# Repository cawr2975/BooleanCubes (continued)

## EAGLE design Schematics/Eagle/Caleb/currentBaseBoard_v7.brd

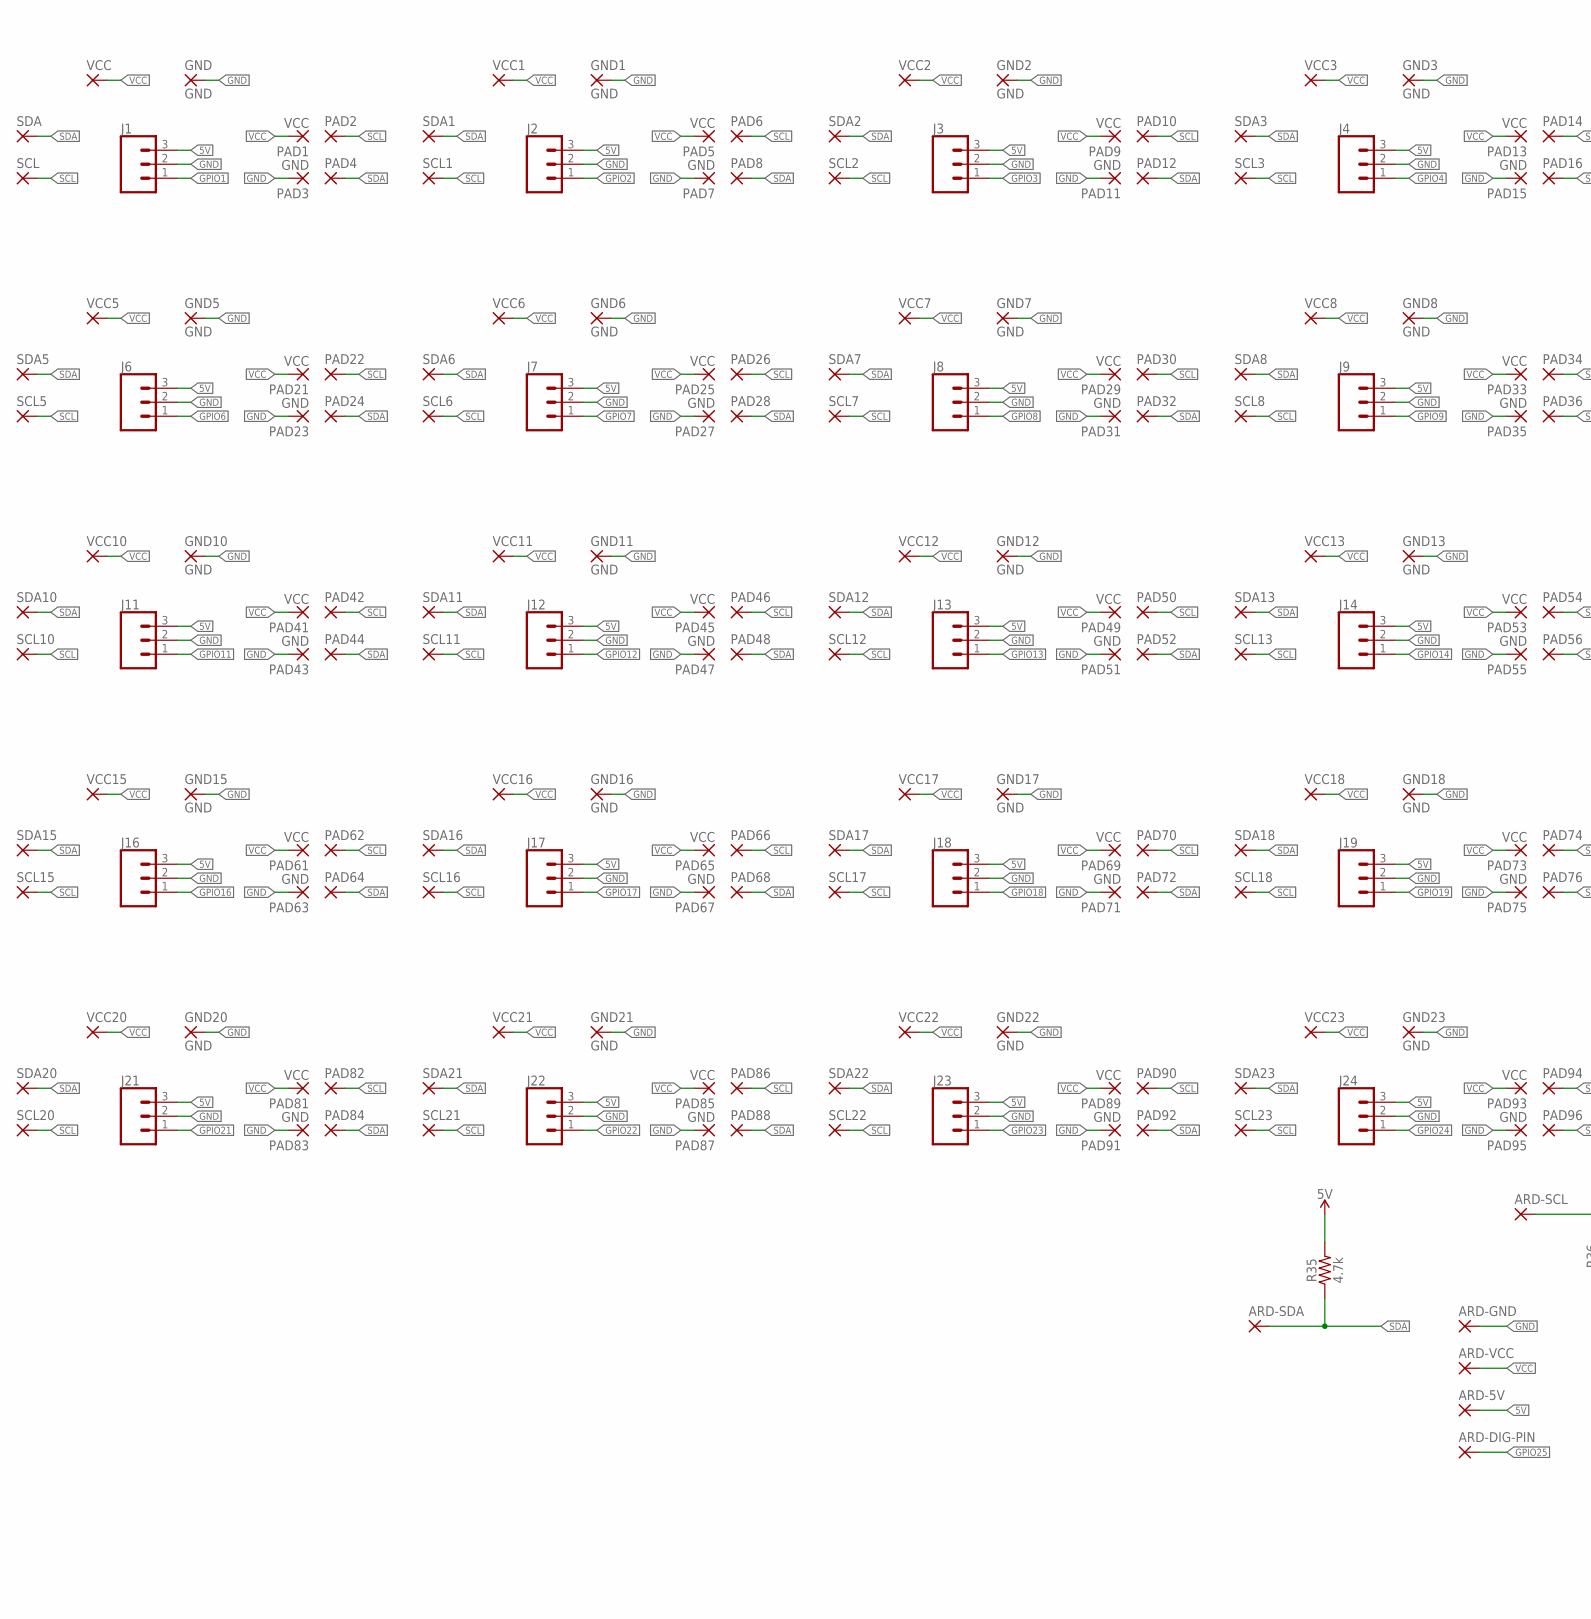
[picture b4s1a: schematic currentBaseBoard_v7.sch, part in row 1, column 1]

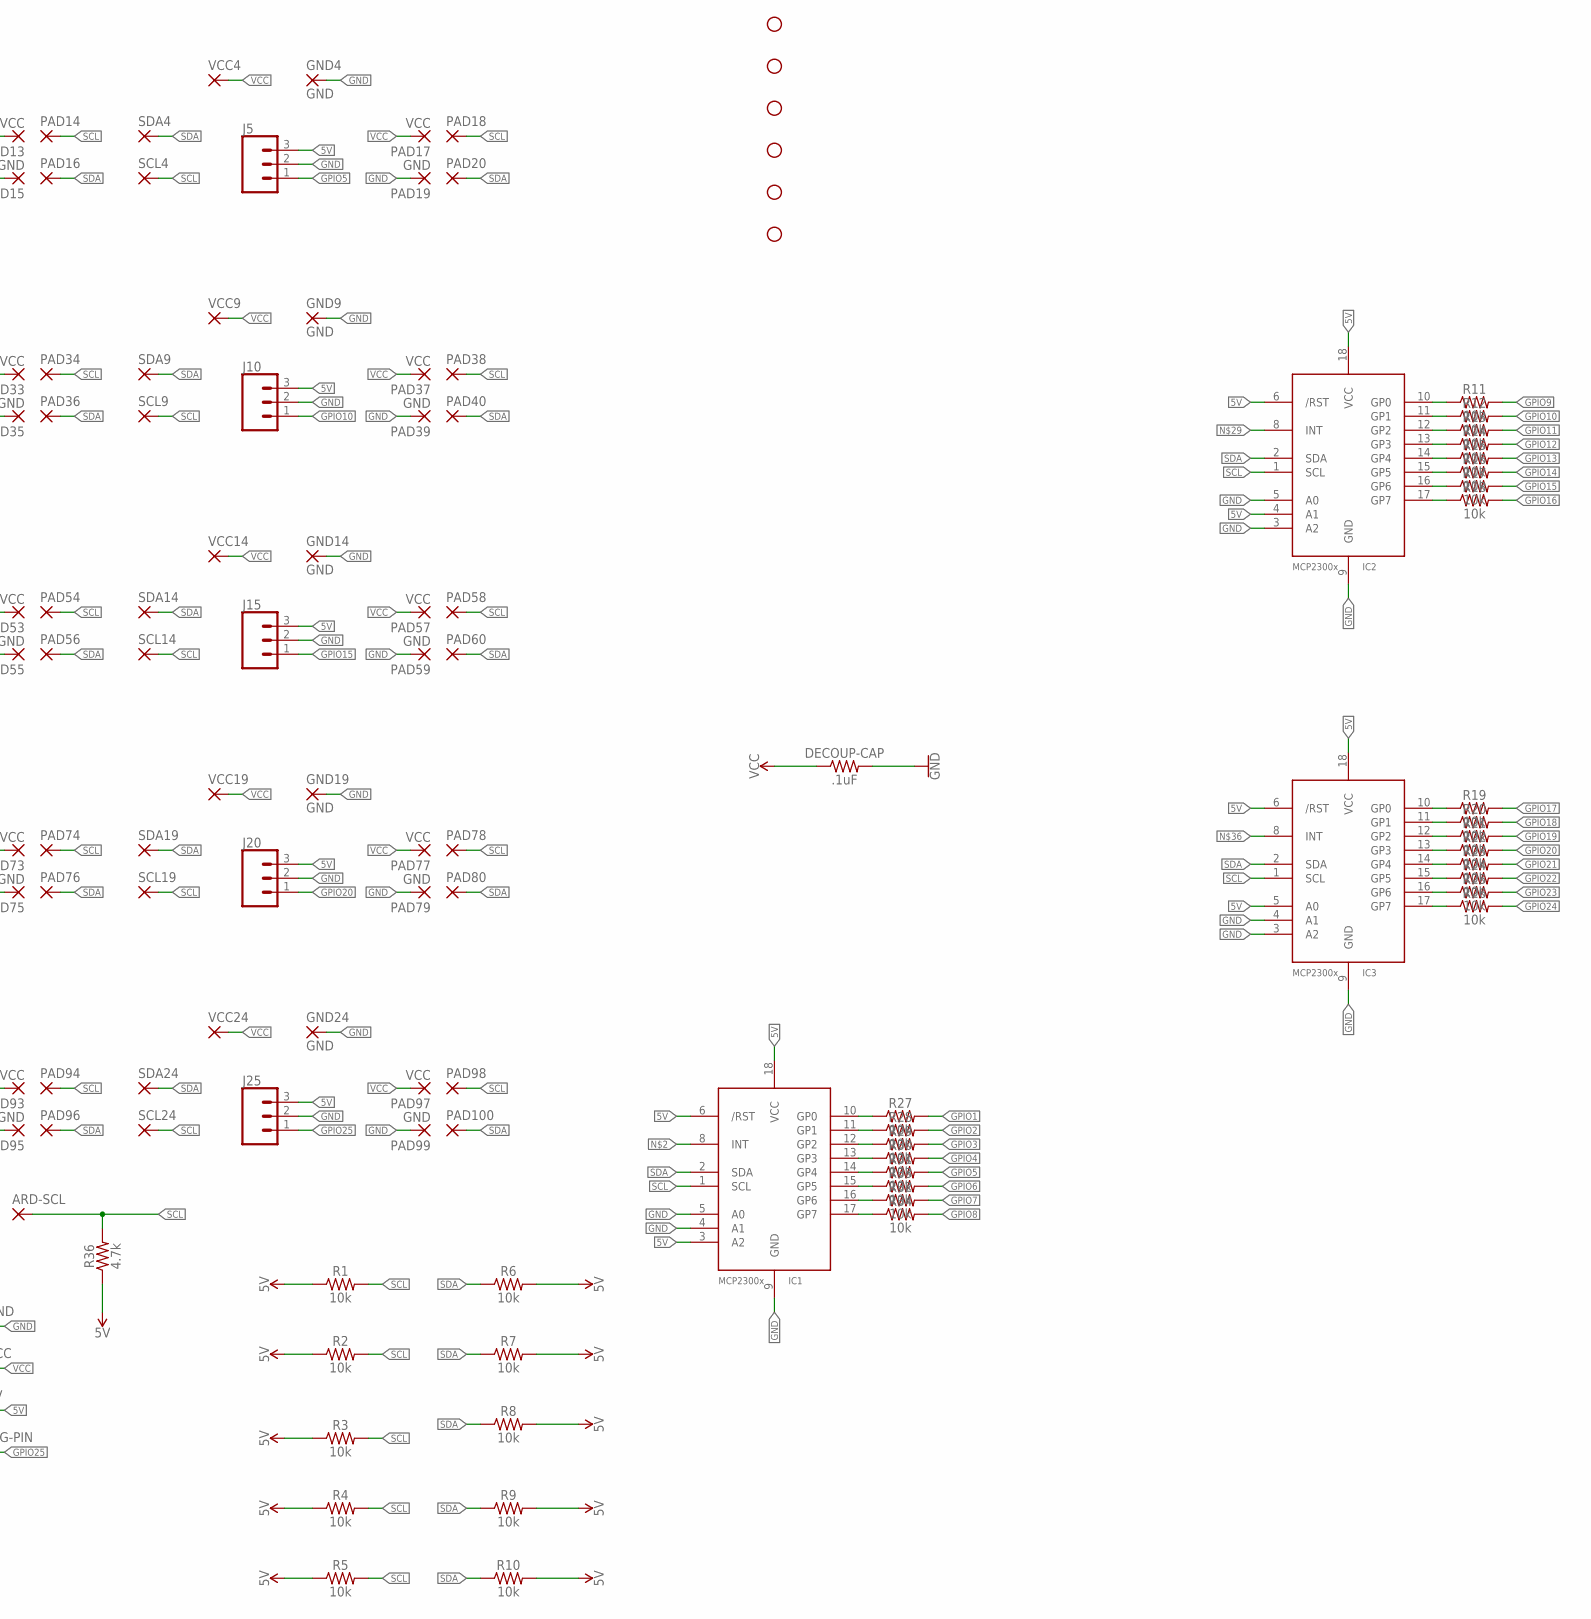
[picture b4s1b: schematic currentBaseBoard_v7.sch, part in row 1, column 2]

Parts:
ARD-5V: 2,15/1,0
ARD-DIG-PIN: 2,15/1,0
ARD-GND: 2,15/1,0
ARD-SCL: 2,15/1,0
ARD-SDA: 2,15/1,0
ARD-VCC: 2,15/1,0
DECOUP-CAP: .1uF; AXIAL-0.3
GND, GND1, GND2, GND3, GND4, GND5, GND6, GND7, GND8, GND9, GND10, GND11, GND12, GND13, GND14, GND15, GND16, GND17, GND18, GND19, GND20, GND21, GND22, GND23, GND24: GND; 2,15/1,0
H1, H2, H3, H4, H5, H6: STAND-OFF
IC1, IC2, IC3: MCP23008/P; DIL18
J1, J2, J3, J4, J5, J6, J7, J8, J9, J10, J11, J12, J13, J14, J15, J16, J17, J18, J19, J20, J21, J22, J23, J24, J25: CONN_03; 1X03
PAD1, PAD5, PAD9, PAD13, PAD17, PAD21, PAD25, PAD29, PAD33, PAD37, PAD41, PAD45, PAD49, PAD53, PAD57, PAD61, PAD65, PAD69, PAD73, PAD77, PAD81, PAD85, PAD89, PAD93, PAD97: VCC; 2,15/1,0
PAD2, PAD4, PAD6, PAD8, PAD10, PAD12, PAD14, PAD16, PAD18, PAD20, PAD22, PAD24, PAD26, PAD28, PAD30, PAD32, PAD34, PAD36, PAD38, PAD40, PAD42, PAD44, PAD46, PAD48, PAD50, PAD52, PAD54, PAD56, PAD58, PAD60, PAD62, PAD64, PAD66, PAD68, PAD70, PAD72, PAD74, PAD76, PAD78, PAD80, PAD82, PAD84, PAD86, PAD88, PAD90, PAD92, PAD94, PAD96, PAD98, PAD100: 2,15/1,0
PAD3, PAD7, PAD11, PAD15, PAD19, PAD23, PAD27, PAD31, PAD35, PAD39, PAD43, PAD47, PAD51, PAD55, PAD59, PAD63, PAD67, PAD71, PAD75, PAD79, PAD83, PAD87, PAD91, PAD95, PAD99: GND; 2,15/1,0
R1, R2, R3, R4, R5, R6, R7, R8, R9, R10, R11, R12, R13, R14, R15, R16, R17, R18, R19, R20, R21, R22, R23, R24, R25, R26, R27, R28, R29, R30, R31, R32, R33, R34: 10k; AXIAL-0.3
R35, R36: 4.7k; AXIAL-0.3
SCL, SCL1, SCL2, SCL3, SCL4, SCL5, SCL6, SCL7, SCL8, SCL9, SCL10, SCL11, SCL12, SCL13, SCL14, SCL15, SCL16, SCL17, SCL18, SCL19, SCL20, SCL21, SCL22, SCL23, SCL24: 2,15/1,0
SDA, SDA1, SDA2, SDA3, SDA4, SDA5, SDA6, SDA7, SDA8, SDA9, SDA10, SDA11, SDA12, SDA13, SDA14, SDA15, SDA16, SDA17, SDA18, SDA19, SDA20, SDA21, SDA22, SDA23, SDA24: 2,15/1,0
VCC, VCC1, VCC2, VCC3, VCC4, VCC5, VCC6, VCC7, VCC8, VCC9, VCC10, VCC11, VCC12, VCC13, VCC14, VCC15, VCC16, VCC17, VCC18, VCC19, VCC20, VCC21, VCC22, VCC23, VCC24: 2,15/1,0

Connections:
5V: ARD-5V.1, IC1.3 (A2), IC1.6 (/RST), IC1.18 (VCC), IC2.4 (A1), IC2.6 (/RST), IC2.18 (VCC), IC3.5 (A0), IC3.6 (/RST), IC3.18 (VCC), J1.3, J2.3, J3.3, J4.3, J5.3, J6.3, J7.3, J8.3, J9.3, J10.3, J11.3, J12.3, J13.3, J14.3, J15.3, J16.3, J17.3, J18.3, J19.3, J20.3, J21.3, J22.3, J23.3, J24.3, J25.3, R1.P$1 (1), R2.P$1 (1), R3.P$1 (1), R4.P$1 (1), R5.P$1 (1), R6.P$2 (2), R7.P$2 (2), R8.P$2 (2), R9.P$2 (2), R10.P$2 (2), R35.P$2 (2), R36.P$1 (1)
GND: ARD-GND.1, DECOUP-CAP.P$2 (2), GND.1, GND1.1, GND2.1, GND3.1, GND4.1, GND5.1, GND6.1, GND7.1, GND8.1, GND9.1, GND10.1, GND11.1, GND12.1, GND13.1, GND14.1, GND15.1, GND16.1, GND17.1, GND18.1, GND19.1, GND20.1, GND21.1, GND22.1, GND23.1, GND24.1, IC1.4 (A1), IC1.5 (A0), IC1.9 (GND), IC2.3 (A2), IC2.5 (A0), IC2.9 (GND), IC3.3 (A2), IC3.4 (A1), IC3.9 (GND), J1.2, J2.2, J3.2, J4.2, J5.2, J6.2, J7.2, J8.2, J9.2, J10.2, J11.2, J12.2, J13.2, J14.2, J15.2, J16.2, J17.2, J18.2, J19.2, J20.2, J21.2, J22.2, J23.2, J24.2, J25.2, PAD3.1, PAD7.1, PAD11.1, PAD15.1, PAD19.1, PAD23.1, PAD27.1, PAD31.1, PAD35.1, PAD39.1, PAD43.1, PAD47.1, PAD51.1, PAD55.1, PAD59.1, PAD63.1, PAD67.1, PAD71.1, PAD75.1, PAD79.1, PAD83.1, PAD87.1, PAD91.1, PAD95.1, PAD99.1
GPIO1: J1.1, R27.P$2 (2)
GPIO2: J2.1, R28.P$2 (2)
GPIO3: J3.1, R29.P$2 (2)
GPIO4: J4.1, R30.P$2 (2)
GPIO5: J5.1, R31.P$2 (2)
GPIO6: J6.1, R33.P$2 (2)
GPIO7: J7.1, R32.P$2 (2)
GPIO8: J8.1, R34.P$2 (2)
GPIO9: J9.1, R11.P$2 (2)
GPIO10: J10.1, R12.P$2 (2)
GPIO11: J11.1, R13.P$2 (2)
GPIO12: J12.1, R14.P$2 (2)
GPIO13: J13.1, R15.P$2 (2)
GPIO14: J14.1, R16.P$2 (2)
GPIO15: J15.1, R17.P$2 (2)
GPIO16: J16.1, R18.P$2 (2)
GPIO17: J17.1, R19.P$2 (2)
GPIO18: J18.1, R20.P$2 (2)
GPIO19: J19.1, R21.P$2 (2)
GPIO20: J20.1, R22.P$2 (2)
GPIO21: J21.1, R23.P$2 (2)
GPIO22: J22.1, R24.P$2 (2)
GPIO23: J23.1, R25.P$2 (2)
GPIO24: J24.1, R26.P$2 (2)
GPIO25: ARD-DIG-PIN.1, J25.1
unnamed: IC1.10 (GP0), R27.P$1 (1)
unnamed: IC1.11 (GP1), R28.P$1 (1)
unnamed: IC1.12 (GP2), R29.P$1 (1)
unnamed: IC1.13 (GP3), R30.P$1 (1)
unnamed: IC1.14 (GP4), R31.P$1 (1)
unnamed: IC1.15 (GP5), R33.P$1 (1)
unnamed: IC1.16 (GP6), R32.P$1 (1)
unnamed: IC1.17 (GP7), R34.P$1 (1)
unnamed: IC2.10 (GP0), R11.P$1 (1)
unnamed: IC2.11 (GP1), R12.P$1 (1)
unnamed: IC2.12 (GP2), R13.P$1 (1)
unnamed: IC2.13 (GP3), R14.P$1 (1)
unnamed: IC2.14 (GP4), R15.P$1 (1)
unnamed: IC2.15 (GP5), R16.P$1 (1)
unnamed: IC2.16 (GP6), R17.P$1 (1)
unnamed: IC2.17 (GP7), R18.P$1 (1)
unnamed: IC3.10 (GP0), R19.P$1 (1)
unnamed: IC3.11 (GP1), R20.P$1 (1)
unnamed: IC3.12 (GP2), R21.P$1 (1)
unnamed: IC3.13 (GP3), R22.P$1 (1)
unnamed: IC3.14 (GP4), R23.P$1 (1)
unnamed: IC3.15 (GP5), R24.P$1 (1)
unnamed: IC3.16 (GP6), R25.P$1 (1)
unnamed: IC3.17 (GP7), R26.P$1 (1)
SCL: ARD-SCL.1, IC1.1 (SCL), IC2.1 (SCL), IC3.1 (SCL), PAD2.1, PAD6.1, PAD10.1, PAD14.1, PAD18.1, PAD22.1, PAD26.1, PAD30.1, PAD34.1, PAD38.1, PAD42.1, PAD46.1, PAD50.1, PAD54.1, PAD58.1, PAD62.1, PAD66.1, PAD70.1, PAD74.1, PAD78.1, PAD82.1, PAD86.1, PAD90.1, PAD94.1, PAD98.1, R1.P$2 (2), R2.P$2 (2), R3.P$2 (2), R4.P$2 (2), R5.P$2 (2), R36.P$2 (2), SCL.1, SCL1.1, SCL2.1, SCL3.1, SCL4.1, SCL5.1, SCL6.1, SCL7.1, SCL8.1, SCL9.1, SCL10.1, SCL11.1, SCL12.1, SCL13.1, SCL14.1, SCL15.1, SCL16.1, SCL17.1, SCL18.1, SCL19.1, SCL20.1, SCL21.1, SCL22.1, SCL23.1, SCL24.1
SDA: ARD-SDA.1, IC1.2 (SDA), IC2.2 (SDA), IC3.2 (SDA), PAD4.1, PAD8.1, PAD12.1, PAD16.1, PAD20.1, PAD24.1, PAD28.1, PAD32.1, PAD36.1, PAD40.1, PAD44.1, PAD48.1, PAD52.1, PAD56.1, PAD60.1, PAD64.1, PAD68.1, PAD72.1, PAD76.1, PAD80.1, PAD84.1, PAD88.1, PAD92.1, PAD96.1, PAD100.1, R6.P$1 (1), R7.P$1 (1), R8.P$1 (1), R9.P$1 (1), R10.P$1 (1), R35.P$1 (1), SDA.1, SDA1.1, SDA2.1, SDA3.1, SDA4.1, SDA5.1, SDA6.1, SDA7.1, SDA8.1, SDA9.1, SDA10.1, SDA11.1, SDA12.1, SDA13.1, SDA14.1, SDA15.1, SDA16.1, SDA17.1, SDA18.1, SDA19.1, SDA20.1, SDA21.1, SDA22.1, SDA23.1, SDA24.1
VCC: ARD-VCC.1, DECOUP-CAP.P$1 (1), PAD1.1, PAD5.1, PAD9.1, PAD13.1, PAD17.1, PAD21.1, PAD25.1, PAD29.1, PAD33.1, PAD37.1, PAD41.1, PAD45.1, PAD49.1, PAD53.1, PAD57.1, PAD61.1, PAD65.1, PAD69.1, PAD73.1, PAD77.1, PAD81.1, PAD85.1, PAD89.1, PAD93.1, PAD97.1, VCC.1, VCC1.1, VCC2.1, VCC3.1, VCC4.1, VCC5.1, VCC6.1, VCC7.1, VCC8.1, VCC9.1, VCC10.1, VCC11.1, VCC12.1, VCC13.1, VCC14.1, VCC15.1, VCC16.1, VCC17.1, VCC18.1, VCC19.1, VCC20.1, VCC21.1, VCC22.1, VCC23.1, VCC24.1

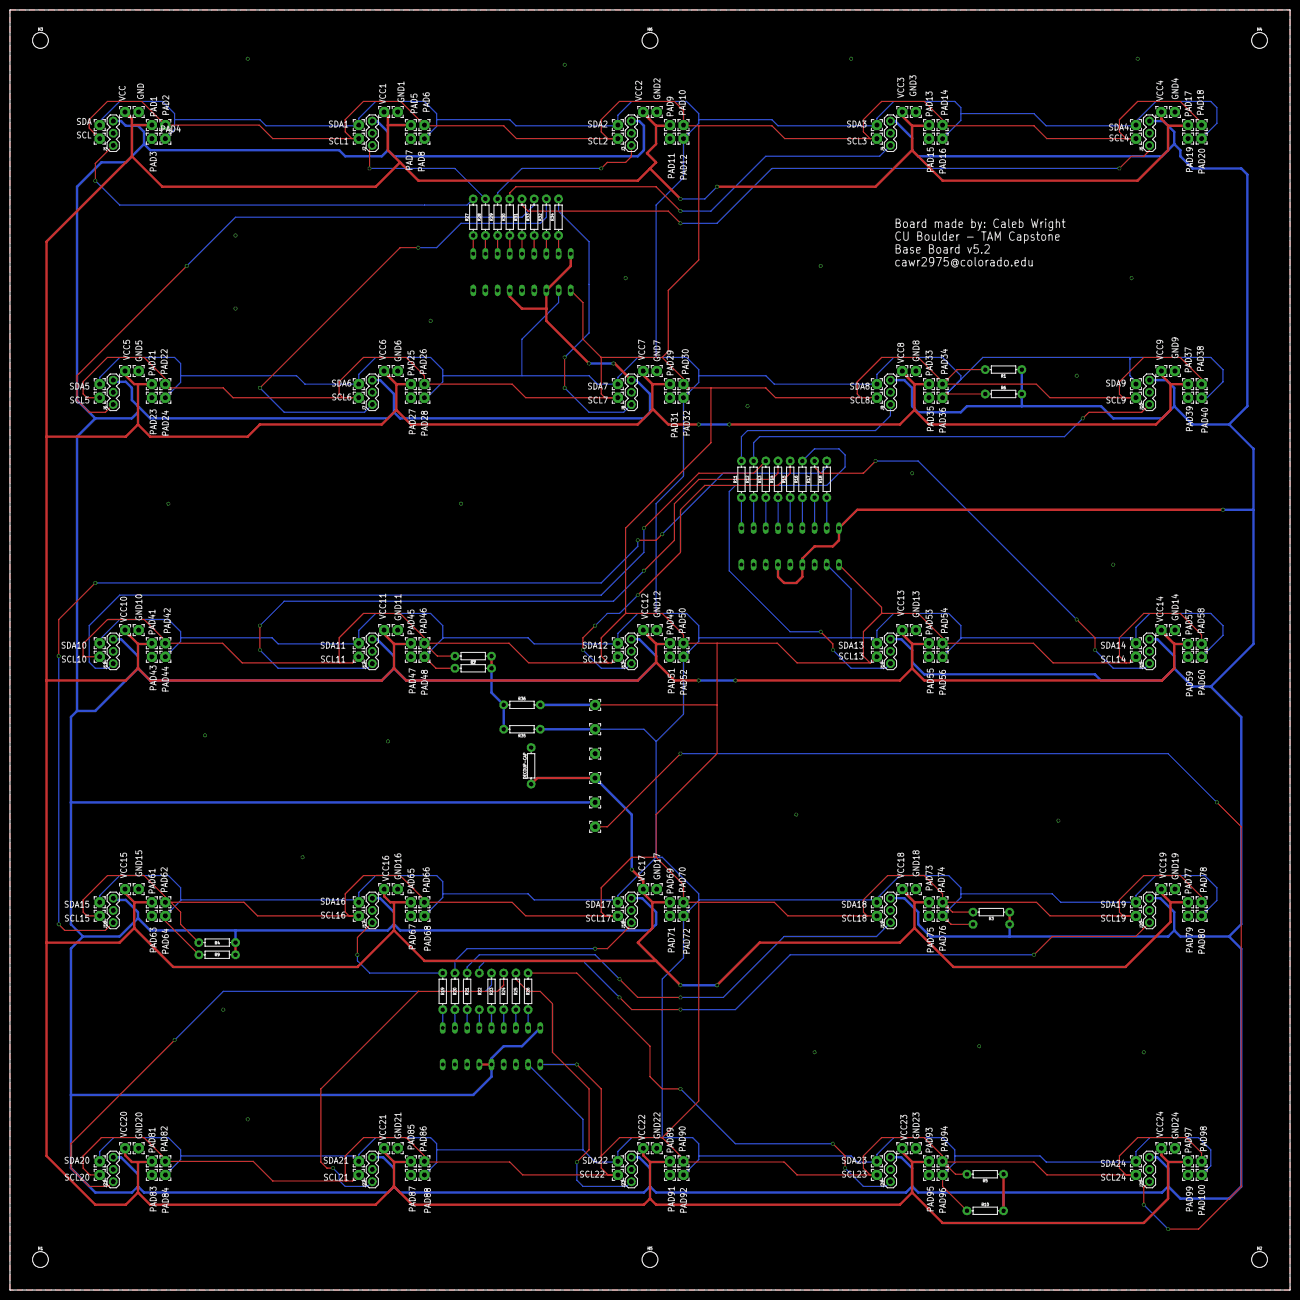
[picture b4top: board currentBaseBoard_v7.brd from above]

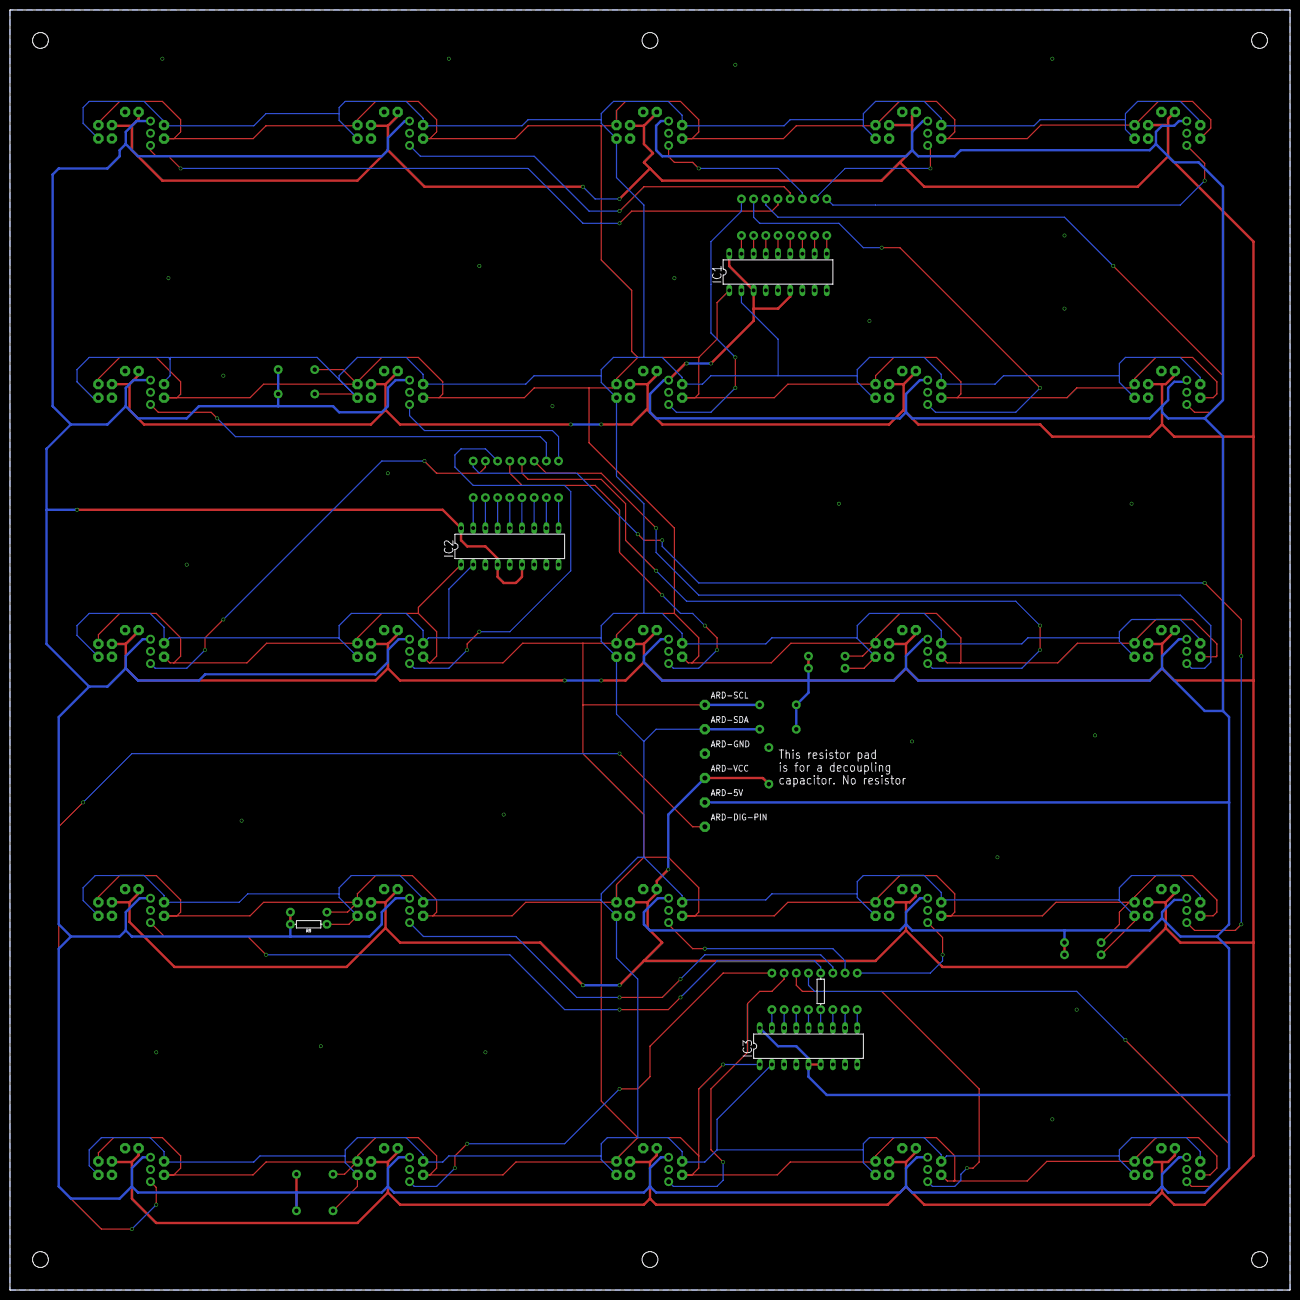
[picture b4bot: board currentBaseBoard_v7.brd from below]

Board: 2 copper layers, 266.7 x 266.7 mm, 277 parts (5 on the bottom side), 54 nets.

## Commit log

2019-12-14 Initial Push - All parts and schematics
2019-12-14 list of parts
